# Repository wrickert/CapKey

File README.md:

I was inspired by HackaDay's Belgrade badge. I wanted to make something like it however I thought the cost and assembly of all those buttons would be a bit much. So I want to abuse a touchpad's capacitive touch controller to make a keyboard. This should be fun.

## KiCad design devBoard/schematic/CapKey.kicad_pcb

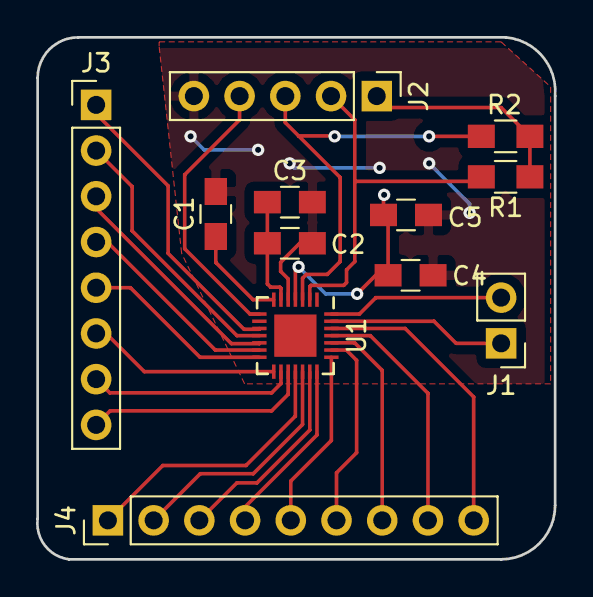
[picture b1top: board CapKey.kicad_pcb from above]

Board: 2 copper layers, 28.8 x 29.0 mm, 12 parts (0 on the bottom side), 26 nets.

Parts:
C1: 100nF; C_0805_HandSoldering
C2, C4: 100pF; C_0805_HandSoldering
C3, C5: 1uF; C_0805_HandSoldering
J1: Other; Pin_Header_Straight_1x02_Pitch2.54mm
J2: I2C data and programming; Pin_Header_Straight_1x05_Pitch2.54mm
J3: RX; Pin_Header_Straight_1x08_Pitch2.54mm
J4: TX; Pin_Header_Straight_1x09_Pitch2.54mm
R1, R2: 4.7K; R_0805_HandSoldering
U1: IQS572; UQFN-28-1EP_4x4mm_Pitch0.4mm

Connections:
+3V3: C4.1, C5.1, J2.1, R1.1, R2.1, U1.4
GND: C1.2, C2.2, C3.2, C4.2, C5.2, J2.5, U1.5
unnamed: C1.1, U1.7
unnamed: C2.1, C3.1, U1.6
PGM: J1.1, U1.27
RDY: J2.4, U1.8
RX0: J3.1, U1.10
RX1: J3.2, U1.11
RX2: J3.3, U1.12
RX3: J3.4, U1.13
RX4: J3.5, U1.14
RX5: J3.6, U1.15
RX6: J3.7, U1.16
RX7: J3.8, U1.17
SCL: J2.3, R2.2, U1.3
SDA: J2.2, R1.2, U1.2
SW_IN: J1.2, U1.28
TX0: J4.1, U1.18
TX1: J4.2, U1.19
TX2: J4.3, U1.20
TX3: J4.4, U1.21
TX4: J4.5, U1.22
TX5: J4.6, U1.23
TX6: J4.7, U1.24
TX7: J4.8, U1.25
TX8: J4.9, U1.26

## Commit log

2018-06-09 Dev board created and sent off to osh park
